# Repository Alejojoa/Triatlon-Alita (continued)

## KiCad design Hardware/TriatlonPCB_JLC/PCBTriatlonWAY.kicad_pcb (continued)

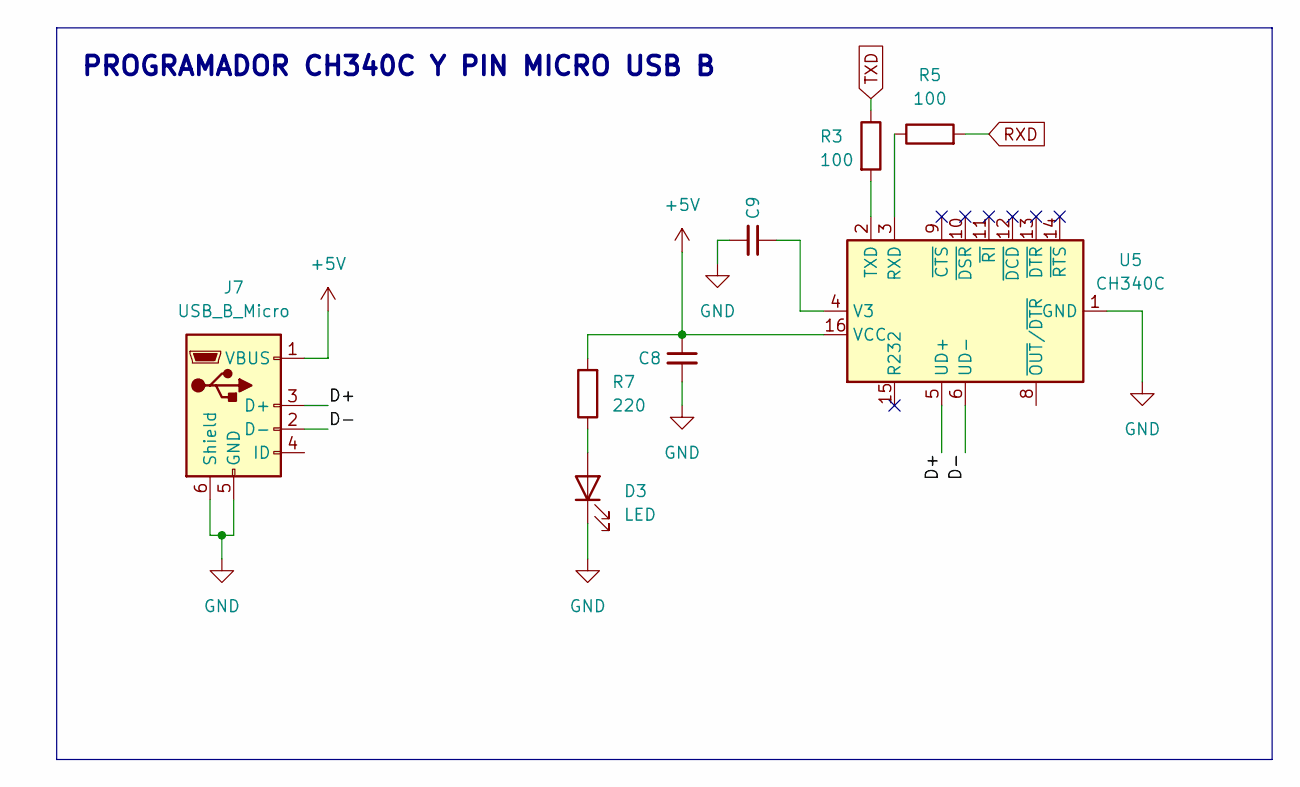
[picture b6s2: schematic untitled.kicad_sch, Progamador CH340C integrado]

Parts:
C8, C9: C_0805_2012Metric_Pad1.18x1.45mm_HandSolder
D3: LED; LED_0805_2012Metric_Pad1.15x1.40mm_HandSolder
J7: USB_B_Micro; USB_Micro-B_Molex-105017-0001
R3, R5: 100; R_0805_2012Metric_Pad1.20x1.40mm_HandSolder
R7: 220; R_0805_2012Metric_Pad1.20x1.40mm_HandSolder
U5: CH340C; SOIC-16_3.9x9.9mm_P1.27mm

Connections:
+5V: C8.1, J7.1 (VBUS), R7.2, U5.16 (VCC); also elsewhere on the board
/Programador CH340/D+: J7.3 (D+), U5.5 (UD+)
/Programador CH340/D-: J7.2 (D-), U5.6 (UD-)
GND: C8.2, C9.2, D3.1 (K), J7.5 (GND), J7.6 (Shield), U5.1 (GND); also elsewhere on the board
unnamed: D3.2 (A), R7.1
unnamed: R5.1, U5.3 (RXD)
unnamed: R3.2, U5.2 (TXD)
unnamed: C9.1, U5.4 (V3)
RXD: R5.2; also elsewhere on the board
TXD: R3.1; also elsewhere on the board

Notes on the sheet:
PROGRAMADOR CH340C Y PIN MICRO USB B

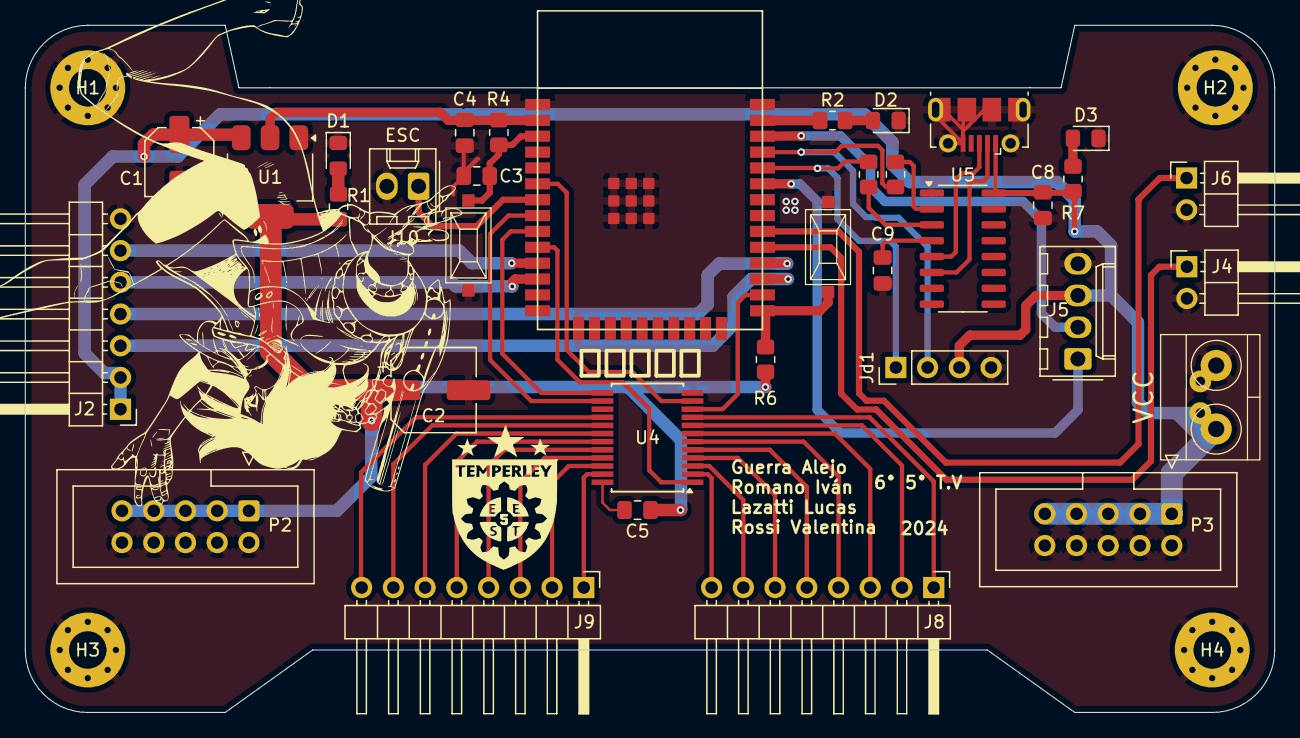
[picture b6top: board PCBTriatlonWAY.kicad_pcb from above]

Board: 2 copper layers, 100.0 x 55.0 mm, 39 parts (0 on the bottom side), 47 nets.

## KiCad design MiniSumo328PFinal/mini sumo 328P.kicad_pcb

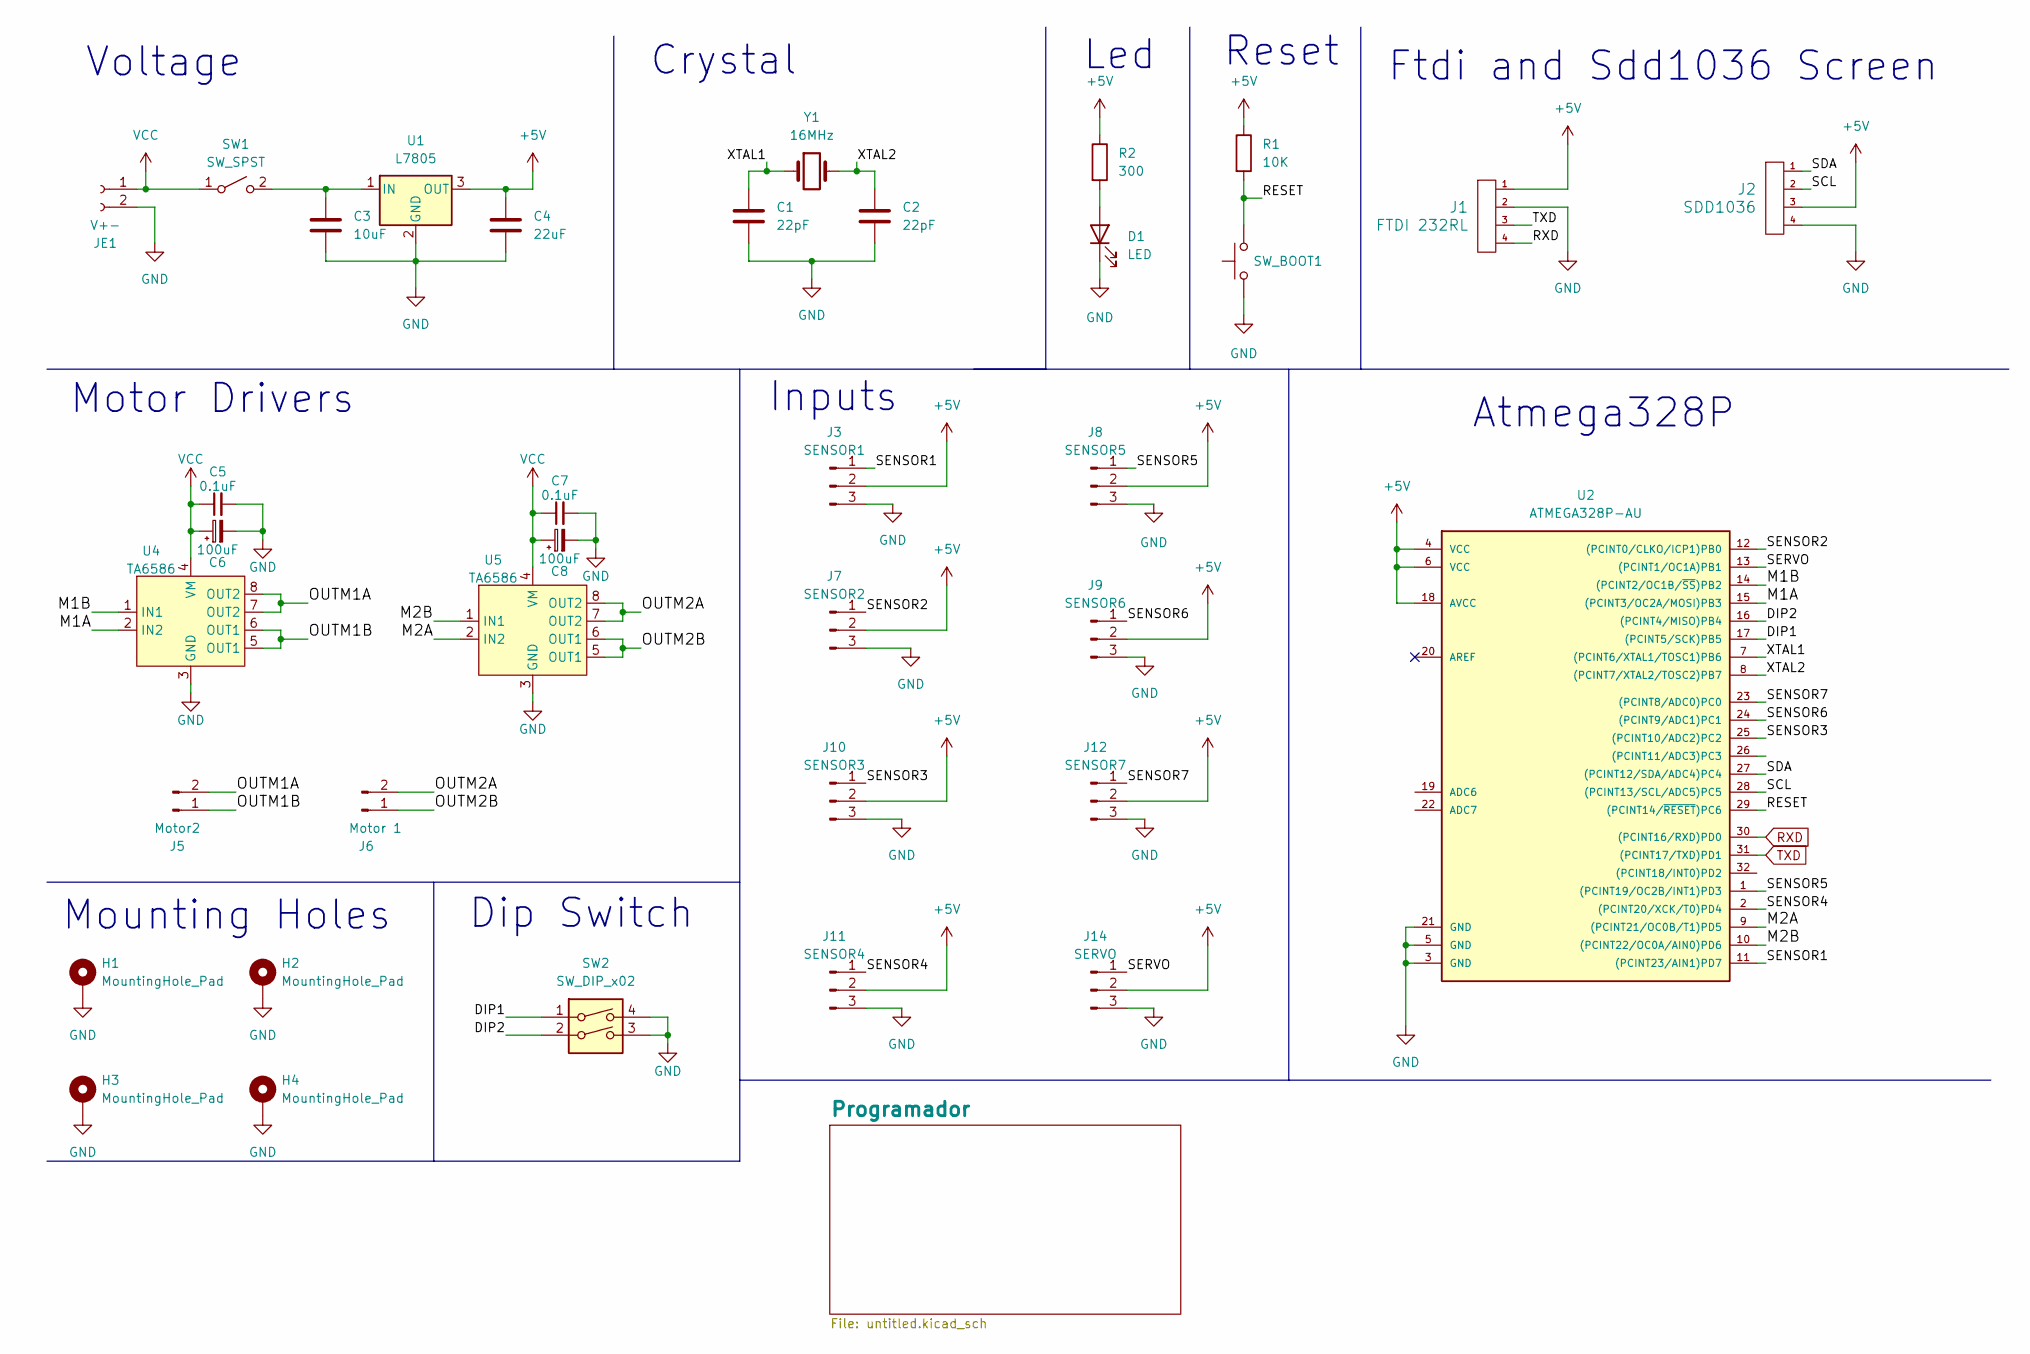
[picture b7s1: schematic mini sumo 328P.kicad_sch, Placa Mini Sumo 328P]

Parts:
C1, C2: 22pF; C_0805_2012Metric_Pad1.18x1.45mm_HandSolder
C3: 10uF; C_0805_2012Metric_Pad1.18x1.45mm_HandSolder
C4: 22uF; C_0805_2012Metric_Pad1.18x1.45mm_HandSolder
C5, C7: 0.1uF; C_0805_2012Metric_Pad1.18x1.45mm_HandSolder
C6, C8: 100uF; CP_EIA-3216-18_Kemet-A_Pad1.58x1.35mm_HandSolder
D1: LED; LED_0805_2012Metric_Pad1.15x1.40mm_HandSolder
H1, H2, H3, H4: MountingHole_Pad; MountingHole_3.2mm_M3_Pad_Via
J1: FTDI 232RL; PinHeader_1x04_P2.54mm_Vertical
J2: SDD1036; PinSocket_1x04_P2.54mm_Vertical
J3: SENSOR1; Smd pad vias x3
J5: Motor2; JST_XH_B2B-XH-A_1x02_P2.50mm_Vertical
J6: Motor 1; JST_XH_B2B-XH-A_1x02_P2.50mm_Vertical
J7: SENSOR2; Smd pad vias x3
J8: SENSOR5; Smd pad vias x3
J9: SENSOR6; Smd pad vias x3
J10: SENSOR3; Smd pad vias x3
J11: SENSOR4; Smd pad vias x3
J12: SENSOR7; Smd pad vias x3
J14: SERVO; PinSocket_1x03_P2.54mm_Vertical
JE1: V+-; BORNERA2_DUO
R1: 10K; R_0805_2012Metric_Pad1.20x1.40mm_HandSolder
R2: 300; R_0805_2012Metric_Pad1.20x1.40mm_HandSolder
SW1: SW_SPST; PinHeader_1x02_P2.54mm_Vertical
SW2: SW_DIP_x02; SW_DIP_SPSTx02_Slide_6.7x6.64mm_W7.62mm_P2.54mm_LowProfile
SW_BOOT1: SW_Push; Pulsador_SMD_2_BAJO
U1: L7805; TO-252-2
U2: ATMEGA328P-AU; TQFP-32_7x7mm_Pitch0.8mm
U4, U5: TA6586; DIP-8_W7.62mm
Y1: 16MHz; Crystal_HC49-4H_Vertical

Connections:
+5V: C4.1, J1.1, J2.3, J3.2, J7.2, J8.2, J9.2, J10.2, J11.2, J12.2, J14.2, R1.1, R2.1, U1.3 (OUT), U2.4 (VCC), U2.6 (VCC), U2.18 (AVCC); also elsewhere on the board
/DIP1: SW2.1, U2.17 ((PCINT5/SCK)PB5)
/DIP2: SW2.2, U2.16 ((PCINT4/MISO)PB4)
/M1A: U2.15 ((PCINT3/OC2A/MOSI)PB3), U4.2 (IN2)
/M1B: U2.14 ((PCINT2/OC1B/~SS)PB2), U4.1 (IN1)
/M2A: U2.9 ((PCINT21/OC0B/T1)PD5), U5.2 (IN2)
/M2B: U2.10 ((PCINT22/OC0A/AIN0)PD6), U5.1 (IN1)
/OUTM1A: J5.2, U4.7 (OUT2), U4.8 (OUT2)
/OUTM1B: J5.1, U4.5 (OUT1), U4.6 (OUT1)
/OUTM2A: J6.2, U5.7 (OUT2), U5.8 (OUT2)
/OUTM2B: J6.1, U5.5 (OUT1), U5.6 (OUT1)
/RESET: R1.2, SW_BOOT1.2, U2.29 ((PCINT14/~RESET)PC6)
/SCL: J2.2, U2.28 ((PCINT13/SCL/ADC5)PC5)
/SDA: J2.1, U2.27 ((PCINT12/SDA/ADC4)PC4)
/SENSOR1: J3.1, U2.11 ((PCINT23/AIN1)PD7)
/SENSOR2: J7.1, U2.12 ((PCINT0/CLKO/ICP1)PB0)
/SENSOR3: J10.1, U2.25 ((PCINT10/ADC2)PC2)
/SENSOR4: J11.1, U2.2 ((PCINT20/XCK/T0)PD4)
/SENSOR5: J8.1, U2.1 ((PCINT19/OC2B/INT1)PD3)
/SENSOR6: J9.1, U2.24 ((PCINT9/ADC1)PC1)
/SENSOR7: J12.1, U2.23 ((PCINT8/ADC0)PC0)
/SERVO: J14.1, U2.13 ((PCINT1/OC1A)PB1)
/XTAL1: C1.1, U2.7 ((PCINT6/XTAL1/TOSC1)PB6), Y1.1
/XTAL2: C2.1, U2.8 ((PCINT7/XTAL2/TOSC2)PB7), Y1.2
GND: C1.2, C2.2, C3.2, C4.2, C5.2, C6.2, C7.2, C8.2, D1.1 (K), H1.1, H2.1, H3.1, H4.1, J1.2, J2.4, J3.3, J7.3, J8.3, J9.3, J10.3, J11.3, J12.3, J14.3, JE1.2, SW2.3, SW2.4, SW_BOOT1.1, U1.2 (GND), U2.3 (GND), U2.5 (GND), U2.21 (GND), U4.3 (GND), U5.3 (GND); also elsewhere on the board
unnamed: D1.2 (A), R2.2
unnamed: C3.1, SW1.2 (B), U1.1 (IN)
RXD: J1.4, U2.30 ((PCINT16/RXD)PD0); also elsewhere on the board
TXD: J1.3, U2.31 ((PCINT17/TXD)PD1); also elsewhere on the board
VCC: C5.1, C6.1, C7.1, C8.1, JE1.1, SW1.1 (A), U4.4 (VM), U5.4 (VM)

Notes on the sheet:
Voltage
Crystal
Mounting Holes
Dip Switch
Ftdi and Sdd1036 Screen
Reset
Motor Drivers
Led
Inputs
Atmega328P

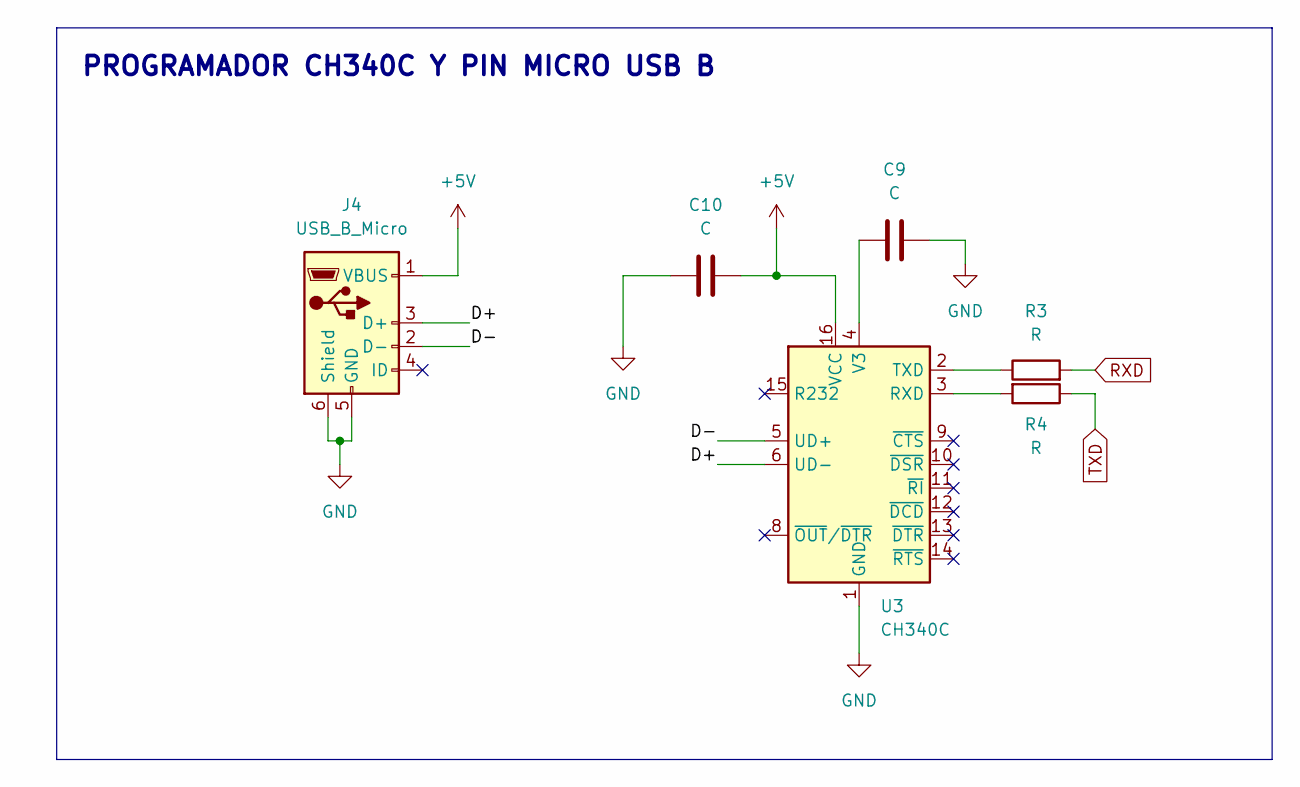
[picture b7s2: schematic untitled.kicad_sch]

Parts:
C9, C10: C; C_0805_2012Metric_Pad1.18x1.45mm_HandSolder
J4: USB_B_Micro; USB_Micro-B_Wuerth_614105150721_Vertical
R3, R4: R; R_0805_2012Metric_Pad1.20x1.40mm_HandSolder
U3: CH340C; SOIC-16_3.9x9.9mm_P1.27mm

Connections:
+5V: C10.2, J4.1 (VBUS), U3.16 (VCC); also elsewhere on the board
/Programador/D+: J4.3 (D+), U3.6 (UD-)
/Programador/D-: J4.2 (D-), U3.5 (UD+)
GND: C9.1, C10.1, J4.5 (GND), J4.6 (Shield), U3.1 (GND); also elsewhere on the board
unnamed: R4.2, U3.3 (RXD)
unnamed: R3.1, U3.2 (TXD)
unnamed: C9.2, U3.4 (V3)
RXD: R3.2; also elsewhere on the board
TXD: R4.1; also elsewhere on the board

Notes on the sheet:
PROGRAMADOR CH340C Y PIN MICRO USB B

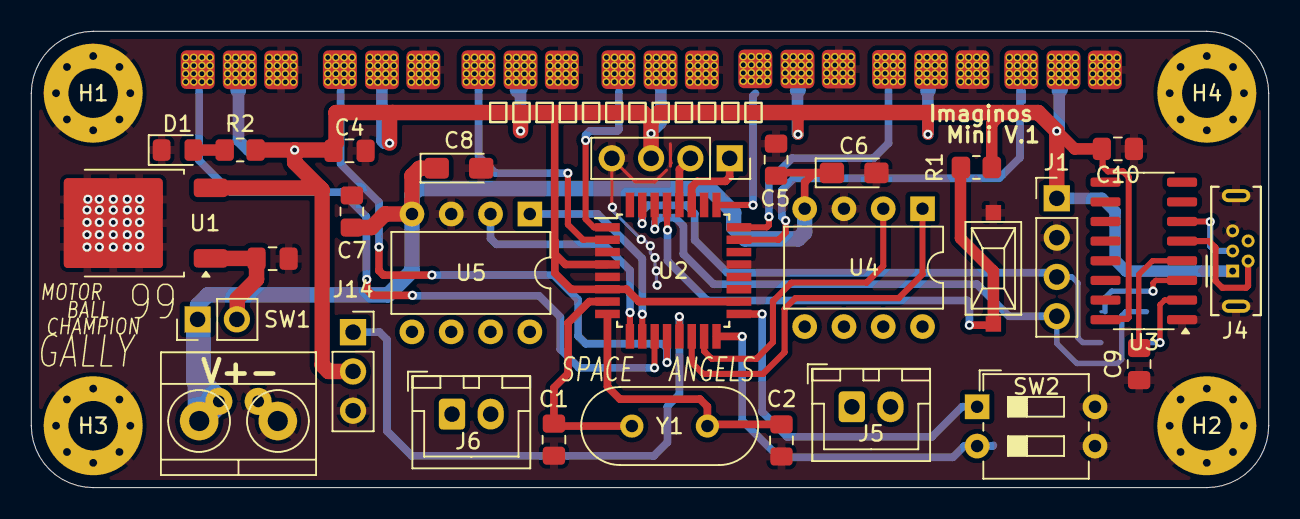
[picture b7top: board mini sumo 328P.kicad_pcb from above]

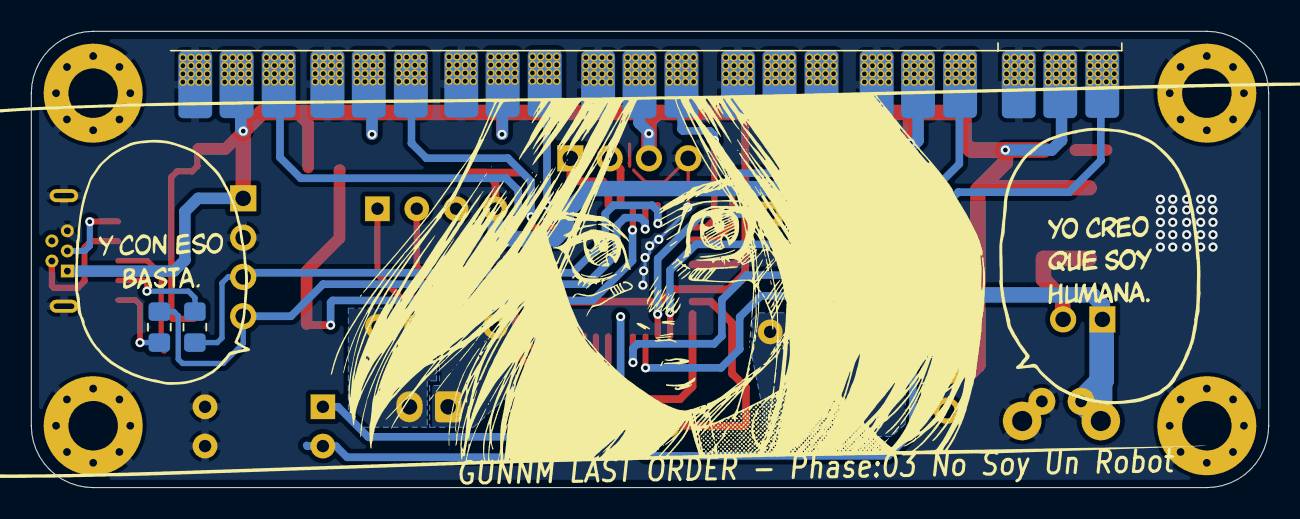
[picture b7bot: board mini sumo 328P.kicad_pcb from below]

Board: 2 copper layers, 80.0 x 29.5 mm, 42 parts (2 on the bottom side), 35 nets.

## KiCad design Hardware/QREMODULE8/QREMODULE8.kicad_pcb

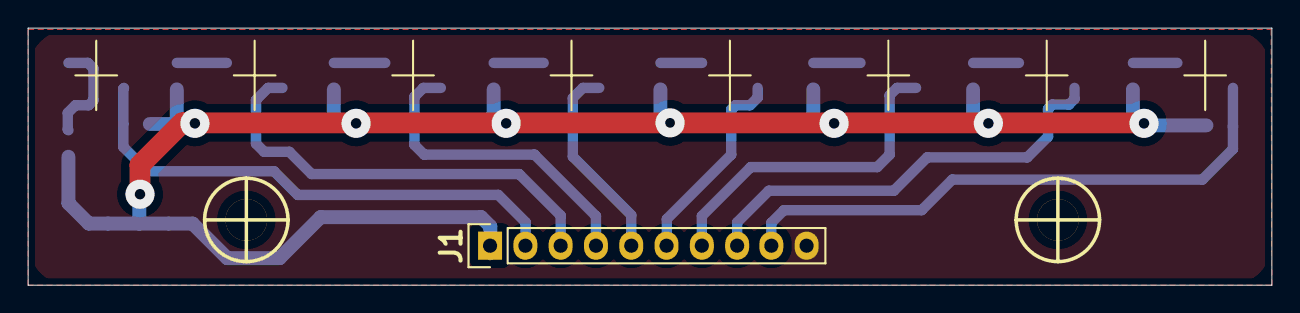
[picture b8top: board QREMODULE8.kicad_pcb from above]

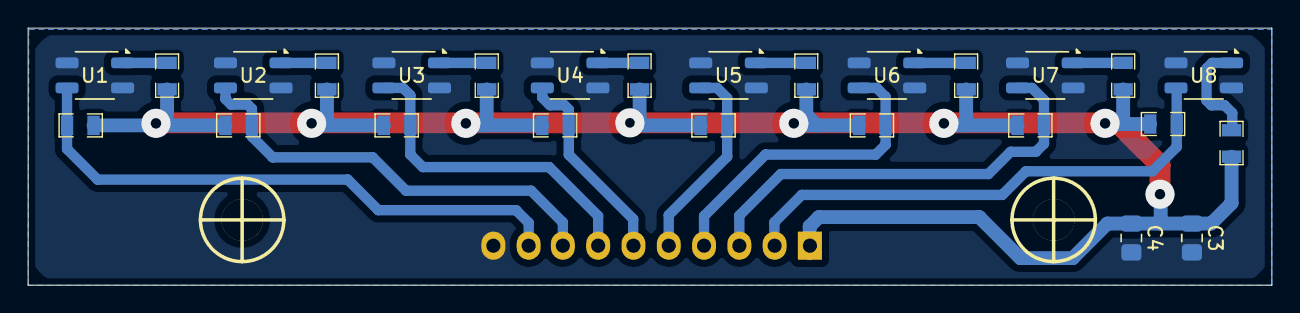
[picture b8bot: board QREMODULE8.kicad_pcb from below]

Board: 2 copper layers, 89.5 x 18.5 mm, 29 parts (26 on the bottom side), 18 nets.

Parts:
C3, C4: 100nf; C_0805_2012Metric_Pad1.18x1.45mm_HandSolder
H1, H2: Mounting_Hole; Separador_M3_10mm
J1: Conn_01x10_Pin; Pin_Header_Straight_1x10
R1, R2, R3, R4, R5, R6, R7, R8, R9, R10, R11, R12, R13, R14, R15, R16: R; R_0805
U1, U2, U3, U4, U5, U6, U7, U8: QRE1113GR; OnSemi_CASE100CY

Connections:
+3V3: C3.1, C4.1, J1.1, R1.1, R2.2, R3.1, R4.2, R5.1, R6.2, R7.1, R8.2, R9.1, R10.1, R11.1, R12.1, R13.2, R14.2, R15.2, R16.2
/OUT1: J1.9, R2.1, U1.3
/OUT2: J1.8, R4.1, U2.3
/OUT3: J1.7, R6.1, U3.3
/OUT4: J1.6, R8.1, U4.3
/OUT5: J1.5, R13.1, U5.3
/OUT6: J1.4, R14.1, U6.3
/OUT7: J1.3, R15.1, U7.3
/OUT8: J1.2, R16.1, U8.3
GND: C3.2, C4.2, J1.10, U1.2 (K), U1.4, U2.2 (K), U2.4, U3.2 (K), U3.4, U4.2 (K), U4.4, U5.2 (K), U5.4, U6.2 (K), U6.4, U7.2 (K), U7.4, U8.2 (K), U8.4
unnamed: R1.2, U1.1 (A)
unnamed: R3.2, U2.1 (A)
unnamed: R5.2, U3.1 (A)
unnamed: R7.2, U4.1 (A)
unnamed: R9.2, U5.1 (A)
unnamed: R10.2, U6.1 (A)
unnamed: R11.2, U7.1 (A)
unnamed: R12.2, U8.1 (A)

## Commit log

2024-04-11 Piezas del robot
    cosas pa imprimir
2024-04-13 Hardware del robot
    Placas Agregadas
    - Qre1113 x8 module
    - Driver TB67H459FNG x2
    //Falta Main board //
2024-04-13 Hardware 3D STL's del robot
    Chasis, brackets, etc del robot
    - Piezas a imprimir
2024-04-13 Delete SUMOTRIATLONMAIN.stl
    xd
2024-04-13 Delete SoporteCentral.stl
    Agregado al Hardware3D
2024-04-13 Delete SoporteDerecho.stl
    Agregado al Hardware3D
2024-04-13 Delete SoporteIzquierdo.stl
    Agregado al Hardware3D
2024-04-13 README.md
    -Foto del robot preview en 3d
    falta lo demas xd
2024-04-15 Delete Hardware/TriatlónPlanB.kicad_pcb
    Añadido en TriatlonB
2024-04-15 Delete Hardware/TriatlónPlanB.kicad_prl
    Añadido en TriatlonB
2024-04-15 Delete Hardware/TriatlónPlanB.kicad_pro
    Añadido en TriatlonB
2024-04-15 Delete Hardware/TriatlónPlanB.kicad_sch
    Añadido en TriatlonB
2024-04-23 Molde de Cubierta
    Molde de rueda para 50mm, total 60mm.
2024-06-04 Cambiando la carpeta Hardware por Firmware.
2024-06-04 Probando que se ya se usar git.
2024-06-05 test commit
2024-06-05 Deshaciendo prueba de jere
2024-06-05 Cambios de la barra de carga
2024-06-10 Probando a commitear desde un archivo de platformio
2024-07-04 Dejando lista la version estable
2024-07-04 Subiendo el main.cpp de romano
2024-07-10 Ordenando funciones
2024-07-29 Agregando codigo de ivan
2024-07-29 Actualización despeja area
2024-08-18 Organización con librerías
2024-08-18 Eliminación de sobrantes
2024-08-18 Actualizando a la última versión de desarrollo
2024-08-19 Eliminando incongruencias
2024-08-20 Cambiando a bluepad (otra vez)
2024-08-21 Actualiizando despeja area
2024-09-06 Reparando
2024-09-06 Eliminando restos
2024-09-06 Reparando .vscode
2024-09-08 Placa Main Para fabricar
    Placa con ESP32, Multiplexor CD74HC4067SM, Programador CH340C
2024-09-16 Preparando rama individual de despeja area
2024-09-16 Corrigiendo
2024-09-16 Actualizando librería motors
2024-09-16 Cambiando librería de motores
2024-09-19 Gerber de la pcb
    Tiene los pines de rx y tx con header, y las conexiones del ch340c switcheadas ( TX a RX - RX a TX)
2024-09-19 Creando rama de testing
2024-09-19 Placa Triatlon
2024-09-19 Other, Placa Minisumo328p
    xd pq subia esto aca
2024-10-10 Orden de directorios y proyecto de KiCad añadido
2024-10-10 Schematid updated
2024-10-10 Placa de drivers añadida
2024-10-11 Avances en esquematico
2024-10-11 Asignacion de huellas
2024-10-12 Primer posicionamiento de componentes en PCB
2024-10-12 Modificacion de footprint y posicionamiento
2024-10-13 Segundo posicionamiento de componentes y ruteo parcial
2024-10-13 Ruteo y PCB completada
2024-10-13 Primera revisión PCB
2024-10-14 PCB_V4: Pinout del ESP32 arreglado
    el driver estaba conectado a los pines de input only jeje
2024-10-14 PCB_V4: conexion a GND de C1 arreglada
2024-10-15 Cambiando a display 1.3' SH1106
2024-10-17 Añadi el simbolo arreglado al esquematico y PCB
2024-10-17 Configurando rama para la modalidad Srinter
2024-10-17 Archivos de Chasis y Ruedas V3
    Hola si leen esto, en algún momento del día díganme pez
2024-10-17 Preparando rama
2024-10-19 Arregle la PCB
    Arregle la PCB lol
2024-10-22 Adaptando al display sh1106
2024-10-22 Cambiando el pinout del multiplexor
2024-10-23 coso
2024-10-23 Agragando PCB plan B
2024-10-23 Acondicionando la PCB nueva
2024-10-23 Adaptando a PCB V2 denuevo
2024-11-20 Finals AreaCleaner Code
2024-11-20 Adjusting minor features
2024-11-20 Making minor changes for 2.0 release
    - Deleted useless comments
    - Deleted unused features
2024-11-20 Making minor changes
    - Deleted useless comments
    - Deleted bluetooth features
    - Fixing indentation and gaps problems
2024-11-20 Making minor changes
    - Deleted useless comments
    - Split menu features apart from other features
    - Replaced some values with constants
2024-11-20 Making minor changes
    - Deleted unused features
    - Added StartModalityTriggers function
2024-11-20 Making minor changes
    - Deleted unused libraries
2024-11-20 Changed from PS3 controller to Bluepad32 library
2024-11-20 Including sumo feature
2024-11-20 Implementing sumo features
2024-11-22 Integrating all features
2024-11-22 Fixing incompatibilities and making minor changes
    - Deleted useless comments
    - Deleted incongruity
2024-11-22 Deleted useless comments
2024-11-22 Transition commit
2024-11-22 Changing "firmware" folder to "Firmware"
2024-11-27 Update README.md
    Las README
